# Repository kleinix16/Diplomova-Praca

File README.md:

# Diplomová práca - Komunikačný systém pre kameramanov

Autor: Bc. Tomáš Klein  
Vedúci práce:  prof. Ing. Juraj Miček, PhD.  
Registračné číslo:  28360820192562  
Rok vydania: Žilina, 2019 

Abstrakt: Diplomová práca sa zaoberá riešením problému komunikácie medzi režisérom a kameramanmi pri vytváraní kamerového záznamu pomocou zariadenia video-strižňa. Práca popisuje vytvorenie komunikačného systému, ktorý bude na kamery prenášať Tally svetelnú signalizáciu využitia kamier a krátke textové správy odosielané z Android zariadenia. V úvode práce je popísaná bezdrôtová komunikácia, so zameraním na bezlicenčné frekvenčné pásma. Ďalej práca obsahuje analýzu zadania, v ktorej je podrobnejšie rozobraný návrh celého systému. Táto časť obsahuje porovnanie a výber komponentov komunikačného systému. Implementačná časť práce sa venuje prepojeniu všetkých analyzovaných komponentov a obsahuje základné postupy a algoritmy, využívané pri riešení. 

Kľúčové slová:  ISM, Tally, Mikrokontrolér, Android, Bluetooth   

Súbory: dokumentácia, zdrojové kódy, android aplikácia, 3D model obalu, schémey, diagramy

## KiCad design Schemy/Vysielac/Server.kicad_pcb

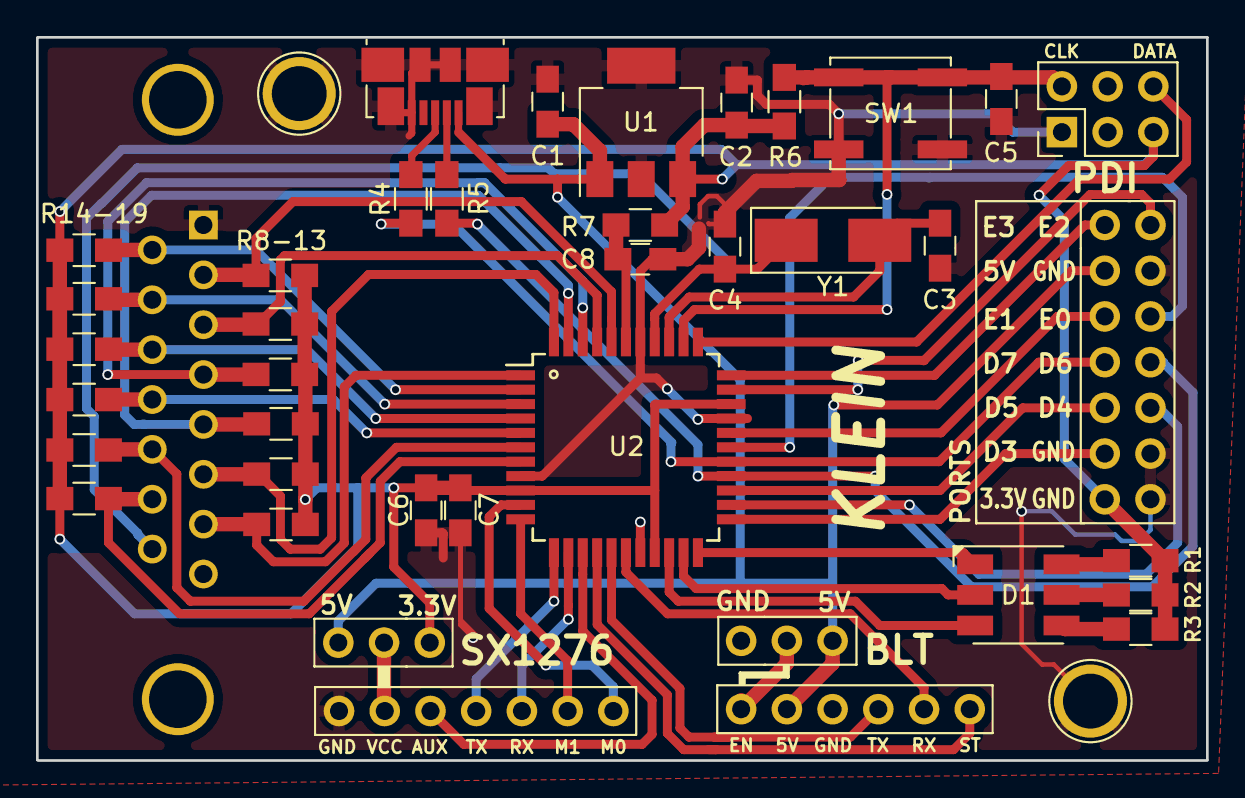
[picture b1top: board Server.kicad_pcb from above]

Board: 2 copper layers, 65.0 x 40.2 mm, 30 parts (0 on the bottom side), 37 nets.

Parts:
 : 1pin
 #2: USB_OTG; USB_Micro-B_Molex_47346-0001
 #3,  #4: Jumper; PIN_3_moj
 #5: PID; PIN_6_moj
 #6: Inter; PIN_12_moj
 #7: BLUETOOTH; PIN_6_moj
 #8: LoRa - SX1276; PIN_7_moj
C1, C5, C7, C8: M1; C_0805_HandSoldering
C2: 22M; C_0805_HandSoldering
C3, C4: C; C_0805_HandSoldering
C6: 2M2; C_0805_HandSoldering
D1: LED_RGB; LED_RGB_5050-6
R1, R2, R3, R4, R5, R14-19: R; R_0805_HandSoldering
R6: M1; R_0805_HandSoldering
R7: 100R; R_0805_HandSoldering
R8-13: 4k7; R_0805_HandSoldering
SW1: RESET; SW_SPST_EVQP0
U1: SOT 233; SOT-223-3_TabPin2
U2: ATXMEGA128A4-AU; CPU_moj
Y1: Crystal; Crystal_SMD_5032-2pin_5.0x3.2mm_HandSoldering

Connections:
+3V3: #3.1, #5.2, #6.13, C2.1, C6.1, C7.1, R1.2, R2.2, R3.2, R6.1, R7.2, R8-13.1, R14-19.1, U1.3, U2.9, U2.19, U2.31
+5V: #2.1, #3.3, #4.3, #6.3, #7.5, C1.1, U1.1
/L1: R14-19.2, U2.2
/R1: R8-13.2, U2.40
AUX_LORA: #8.5, U2.14
B_LED: D1.1, U2.22
GND: .1, #2.5, #2.6, #4.1, #5.6, #6.4, #6.12, #6.14, #7.4, #8.7, C1.2, C2.2, C3.1, C4.1, C5.1, C6.2, C7.2, C8.2, SW1.1, U1.2, U2.8, U2.18, U2.30, U2.38
G_LED: D1.2, U2.21
M0_LORA: #8.1, U2.10
M1_LORA: #8.2, U2.11
unnamed: C3.2, U2.36, Y1.2
unnamed: C4.2, U2.37, Y1.1
unnamed: C8.1, R7.1, U2.39
unnamed: D1.4, R3.1
unnamed: D1.5, R2.1
unnamed: D1.6, R1.1
unnamed: #2.2, R5.2
unnamed: #2.3, R4.2
unnamed: #4.2, #7.6
unnamed: #3.2, #8.6
PD3: #6.11, U2.23
PD4: #6.10, U2.24
PD5: #6.9, U2.25
PD6: #6.8, R5.1, U2.26
PD7: #6.7, R4.1, U2.27
PDI_CLK: #5.5, C5.2, R6.2, SW1.2, U2.35
PDI_DATA: #5.1, U2.34
PE0: #6.6, U2.28
PE1: #6.5, U2.29
PE2: #6.2, U2.32
PE3: #6.1, U2.33
RX_BLT: #7.2, U2.17
RX_LORA: #8.3, U2.13
R_LED: D1.3, U2.20
STATE_BLT: #7.1, U2.15
TX_BLT: #7.3, U2.16
TX_LORA: #8.4, U2.12

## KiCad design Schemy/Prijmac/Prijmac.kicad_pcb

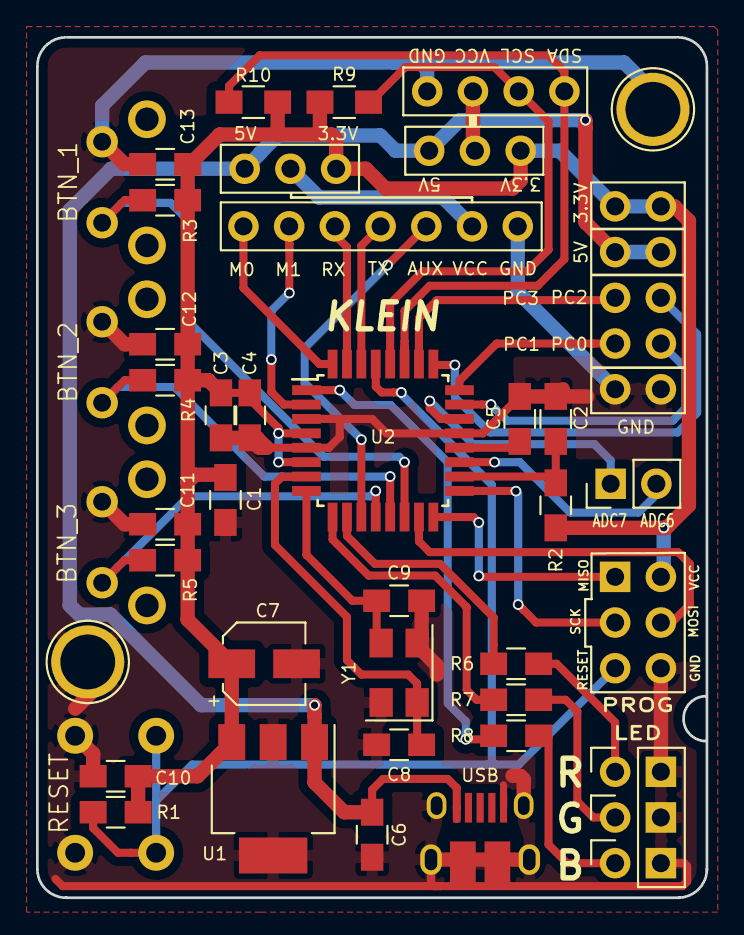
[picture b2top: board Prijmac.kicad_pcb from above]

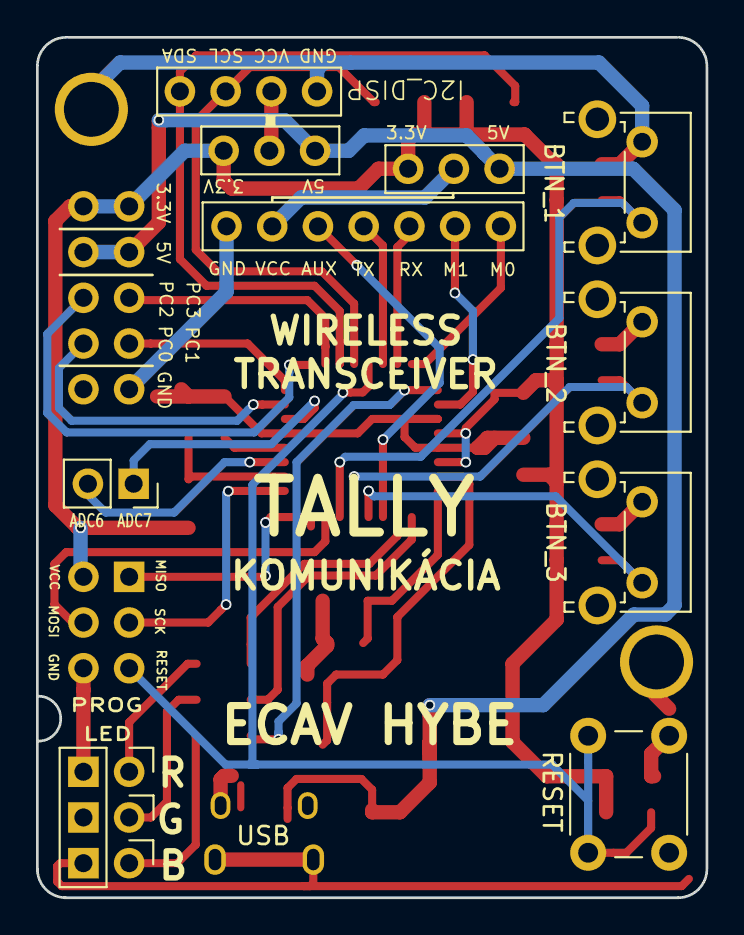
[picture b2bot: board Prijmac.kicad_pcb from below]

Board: 2 copper layers, 37.2 x 47.8 mm, 39 parts (5 on the bottom side), 35 nets.

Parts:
BTN_1, BTN_2, BTN_3: SW_Push; SW_Tactile_SPST_Angled_PTS645Vx83-2LFS
C1, C2, C4, C5, C6, C10, C11, C12, C13: M1; C_0805_HandSoldering
C3: 2M2; C_0805_HandSoldering
C7: 22M; CP_Elec_4x5.8
C8, C9: 18pF; C_0805_HandSoldering
J1: USB_OTG; USB_Micro-B_10103594-0001LF
J2: Analog_only; Pin_Header_Straight_1x02_Pitch2.54mm
J3: PROG; Pin_Header_Straight_2x03_Pitch2.54mm
J4: EXT; Pin_Header_Straight_2x05_Pitch2.54mm
J5: LEDS; Pin_Header_Straight_2x03_Pitch2.54mm
J6: LoRa - RFM; Pin_Header_Straight_1x07_Pitch2.54mm
J7: DISPLAY_I2C; Pin_Header_Straight_1x04_Pitch2.54mm
JP1, JP2: Jumper; Pin_Header_Straight_1x03_Pitch2.54mm
R1, R3, R4, R5, R6, R7, R8: R; C_0805_HandSoldering
R2: 100R; C_0805_HandSoldering
R9, R10: R; R_0805_HandSoldering
RESET: RESET; SW_PUSH_6mm
U1: SOT 233; SOT-223-3_TabPin2
U2: ATMEGA328P-AU; TQFP-32_7x7mm_Pitch0.8mm
Y1: Crystal_GND24; Crystal_SMD_5032-4pin_5.0x3.2mm

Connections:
+3V3: C1.1, C3.1, C4.1, C7.1, C10.1, C11.1, C12.1, C13.1, J3.2, J4.1, J4.2, JP1.1, JP2.1, R1.2, R2.2, R3.2, R4.2, R5.2, R9.1, R10.1, U1.3, U2.4, U2.6
+5V: C6.1, J1.1, J4.3, J4.4, JP1.3, JP2.3, U1.1
AUX_LORA: J6.5, U2.11
BTN_1: BTN_1.2, R3.1, U2.14
BTN_2: BTN_2.2, R4.1, U2.13
BTN_3: BTN_3.2, R5.1, U2.12
B_LED: R8.2, U2.1
GND: BTN_1.1, BTN_2.1, BTN_3.1, C1.2, C2.1, C3.2, C4.2, C5.1, C6.2, C7.2, C8.2, C9.2, C10.2, C11.2, C12.2, C13.2, J1.5, J1.6, J3.6, J4.9, J4.10, J5.2, J5.4, J5.6, J6.7, J7.4, RESET.1, U1.2, U2.3, U2.5, U2.21, Y1.2, Y1.4
G_LED: R7.2, U2.9
M0_LORA: J6.1, U2.32
M1_LORA: J6.2, U2.2
unnamed: C2.2, R2.1, U2.18
unnamed: C5.2, U2.20
unnamed: C8.1, U2.7, Y1.1
unnamed: C9.1, U2.8, Y1.3
unnamed: J2.1, U2.22
unnamed: J2.2, U2.19
unnamed: J3.1, U2.16
unnamed: J3.3, U2.17
unnamed: J3.4, U2.15
unnamed: J5.1, R6.1
unnamed: J5.3, R7.1
unnamed: J5.5, R8.1
unnamed: J6.6, JP1.2
unnamed: J7.3, JP2.2
PC0: J4.8, U2.23
PC1: J4.7, U2.24
PC2: J4.6, U2.25
PC3: J4.5, U2.26
RESET: J3.5, R1.1, RESET.2, U2.29
RX_LORA: J6.3, U2.31
R_LED: R6.2, U2.10
SCL: J7.2, R9.2, U2.28
SDA: J7.1, R10.2, U2.27
TX_LORA: J6.4, U2.30

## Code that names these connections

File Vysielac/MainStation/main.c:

/*
 * MainStation.c
 *
 * Created: 12/22/2018 10:14:10 AM
 * Author : klein
 */

#include "avr_compiler.h"
#include "board.h"
#include "usart_driver.h"
#include "port_driver.h"
#include "TC_driver.h"

#include <util/delay.h>
#include <stdio.h>
#include <string.h>
#include <avr/io.h>

//USART riesim za pomoci dodavanych zdrojakov -projekt AVR1522 - 2 task

//RFM
//USART_RFM Defines
#define USART_RFM USARTC0
#define USART_PORT_RFM PORTC

/* USART data struct used in task */
USART_data_t USART_data_RFM;

//PC
//USART_PC Defines
#define USART_PC USARTE0
#define USART_PORT_PC PORTE

/* USART data struct used in task */
USART_data_t USART_data_PC;
/*
volatile	uint8_t port_A;   //Ulozena posledna hodnota na porte A
volatile	uint8_t port_B;	  //Ulozena posledna hodnota na porte B*/

volatile uint8_t STATE = 0x00;     // Bajt hovoriaci o dovode, preco sa sprava odoslala
volatile uint8_t CAM_READY = 0x00; // Cislo kamery v pripravnom rezime
volatile uint8_t CAM_LIVE = 0x00;  // Cislo kamery v ostrom vyslieani

volatile uint8_t port_A;
volatile uint8_t port_B;

void setTally_CONN()
{
    PORTA.PIN1CTRL = PORT_OPC_PULLUP_gc;
    PORTA.PIN2CTRL = PORT_OPC_PULLUP_gc;
    PORTA.PIN3CTRL = PORT_OPC_PULLUP_gc;
    PORTA.PIN4CTRL = PORT_OPC_PULLUP_gc;
    PORTA.PIN5CTRL = PORT_OPC_PULLUP_gc;
    PORTA.PIN6CTRL = PORT_OPC_PULLUP_gc;
    PORTA.PIN7CTRL = PORT_OPC_PULLUP_gc;
    PORTA.PIN0CTRL = PORT_OPC_PULLUP_gc;
    PORTB.PIN0CTRL = PORT_OPC_PULLUP_gc;
    PORTB.PIN1CTRL = PORT_OPC_PULLUP_gc;
    PORTB.PIN2CTRL = PORT_OPC_PULLUP_gc;
    PORTB.PIN3CTRL = PORT_OPC_PULLUP_gc;

    PORT_SetPinsAsInput(&PORTA, 0xFF);
    PORT_SetPinsAsInput(&PORTB, 0x0F);
}

void setUp_RFM_USART()
{
    /*
	 *    USART configuration:
	 *      - 8 bit character size
	 *      - No parity
	 *      - 1 stop bit
	 *      - 9600 Baud
	 */

    /* PC3 (TXD0) as output. */
    USART_PORT_RFM.DIRSET = PIN3_bm;

    /* PC2 (RXD0) as input. */
    USART_PORT_RFM.DIRCLR = PIN2_bm;

    /* M0 - nastavenie na nulu */
    USART_PORT_RFM.DIRSET = PIN0_bm;
    USART_PORT_RFM.OUTCLR = PIN0_bm;

    /* M1 - nastavenie na nulu */
    USART_PORT_RFM.DIRSET = PIN1_bm;
    USART_PORT_RFM.OUTCLR = PIN1_bm;

    /* Use USARTx0 and initialize buffers */
    USART_InterruptDriver_Initialize(&USART_data_RFM, &USART_RFM, USART_DREINTLVL_LO_gc);

    /* USART, 8 Data bits, No Parity, 1 Stop bit. */
    USART_Format_Set(&USART_RFM, USART_CHSIZE_8BIT_gc, USART_PMODE_DISABLED_gc, false);

    /* Enable RXC interrupt */
    //USART_RxdInterruptLevel_Set(USART_data_RFM.usart, USART_RXCINTLVL_LO_gc);
    USART_RxdInterruptLevel_Set(&USART_RFM, USART_RXCINTLVL_LO_gc);

    /* Set Baudrate to 9600 bps:
	 * Use the default I/O clock fequency that is 2 MHz.
	 * Do not use the baudrate scale factor
	 *
	 * Baudrate select = (1/(16*(((I/O clock frequency)/Baudrate)-1)
	 *                 = 12
	 */
    USART_Baudrate_Set(&USART_RFM, 12, 0);

    /* Enable both RX and TX. */
    USART_Rx_Enable(&USART_RFM);
    USART_Tx_Enable(&USART_RFM);
}

void setUp_PC_USART()
{
    /*
	 *    USART configuration:
	 *      - 8 bit character size
	 *      - No parity
	 *      - 1 stop bit
	 *      - 9600 Baud
	 */

    /* PE3 (TXD0) as output. */
    USART_PORT_PC.DIRSET = PIN3_bm;

    /* PE2 (RXD0) as input. */
    USART_PORT_PC.DIRCLR = PIN2_bm;

    /* Use USARTx0 and initialize buffers */
    USART_InterruptDriver_Initialize(&USART_data_PC, &USART_PC, USART_DREINTLVL_LO_gc);

    /* USART, 8 Data bits, No Parity, 1 Stop bit. */
    USART_Format_Set(&USART_PC, USART_CHSIZE_8BIT_gc, USART_PMODE_DISABLED_gc, false);

    /* Enable RXC interrupt */
    //USART_RxdInterruptLevel_Set(USART_data_RFM.usart, USART_RXCINTLVL_LO_gc);
    USART_RxdInterruptLevel_Set(&USART_PC, USART_RXCINTLVL_LO_gc);

    /* Set Baudrate to 9600 bps:
	 * Use the default I/O clock fequency that is 2 MHz.
	 * Do not use the baudrate scale factor
	 *
	 * Baudrate select = (1/(16*(((I/O clock frequency)/Baudrate)-1)
	 *                 = 12
	 */
    USART_Baudrate_Set(&USART_PC, 12, 0);

    /* Enable both RX and TX. */
    USART_Rx_Enable(&USART_PC);
    USART_Tx_Enable(&USART_PC);
}

void setTimer_Beacon()
{
    /* Set the TC period. */  
    TC_SetPeriod(&TCC0, 0x2710); //5000ms

    /* Enable overflow interrupt at low level */
    TC0_SetOverflowIntLevel(&TCC0, TC_OVFINTLVL_LO_gc);

    /* Start Timer/Counter. */
    TC0_ConfigClockSource(&TCC0, TC_CLKSEL_DIV1024_gc);
}


void setTimer_Tally()
{
    /* Set the TC period. */
    TC_SetPeriod(&TCC1, 0x0190);  //200ms

    /* Enable overflow interrupt at low level */
    TC1_SetOverflowIntLevel(&TCC1, TC_OVFINTLVL_LO_gc);

    /* Start Timer/Counter. */
    TC1_ConfigClockSource(&TCC1, TC_CLKSEL_DIV1024_gc);
	
}

void sendStatus_RFM()
{

    while (!(USARTC0_STATUS & USART_DREIF_bm))
        ; //Wait until DATA buffer is empty

    USARTC0_DATA = STATE;

    while (!(USARTC0_STATUS & USART_DREIF_bm))
        ; //Wait until DATA buffer is empty

    USARTC0_DATA = CAM_LIVE;

    while (!(USARTC0_STATUS & USART_DREIF_bm))
        ; //Wait until DATA buffer is empty

    USARTC0_DATA = CAM_READY;
	
	while (!(USARTC0_STATUS & USART_DREIF_bm))
	; //Wait until DATA buffer is empty

	USARTC0_DATA = 'a';

/*
    while (!(USARTC0_STATUS & USART_DREIF_bm))
        ; //Wait until DATA buffer is empty

    USARTC0_DATA = '\n';

    while (!(USARTC0_STATUS & USART_DREIF_bm))
        ; //Wait until DATA buffer is empty

    USARTC0_DATA = '\r';
	*/

    STATE = 0;
}

void sendChar(char c)
{

    while (!(USARTC0_STATUS & USART_DREIF_bm))
        ; //Wait until DATA buffer is empty

    USARTC0_DATA = c;
}

void sendString(char *text)
{
    while (*text)
    {
        sendChar(*text++);
    }
}

int main(void)
{
    setUp_RFM_USART();

    setUp_PC_USART();

    setTimer_Beacon();
	
	setTimer_Tally();



    // Enable all interrupt levels in PMIC and enable global interrupts.
    PMIC.CTRL |= PMIC_LOLVLEN_bm | PMIC_MEDLVLEN_bm | PMIC_HILVLEN_bm;
    sei();

    while (1)
    {
        if (STATE == 1 || STATE == 2)
        {
            sendStatus_RFM();
        }
        _delay_ms(20);

        /*
	   	  if (USART_RXBufferData_Available(&USART_data_PC))
	   	  {
		   	  sendChar(USART_RXBuffer_GetByte(&USART_data_PC));	  
	   	  }*/
    }
}

/*! \brief Receive complete interrupt service routine.
 *
 *  Receive complete interrupt service routine.
 *  Calls the common receive complete handler with pointer to the correct USART
 *  as argument.
 */
ISR(USARTC0_RXC_vect)
{
    USART_RXComplete(&USART_data_RFM);
}

ISR(USARTE0_RXC_vect)
{
    USART_RXComplete(&USART_data_PC);
}

ISR(USARTC0_DRE_vect)
{
    USART_DataRegEmpty(&USART_data_RFM);
}

ISR(USARTE0_DRE_vect)
{
    USART_DataRegEmpty(&USART_data_PC);
}

// Tell compiler to associate this interrupt handler with the TCC0_OVF_vect vector.
ISR(TCC1_OVF_vect) // TALLY
{
    uint8_t port_A_temp = PORT_GetPortValue(&PORTA);
    uint8_t port_B_temp = PORT_GetPortValue(&PORTB);

    if (port_A_temp != port_A || port_B_temp != port_B)
    {
        port_A = port_A_temp;
        port_B = port_B_temp;

        CAM_LIVE = ((port_A & 0xC0) >> 2) + port_B;
        CAM_READY = port_A >> 2;

        STATE = 2; //Odoslanie dat pri zmene na portoch
		TC_Restart( &TCC0 );
    }
}

ISR(TCC0_OVF_vect) // BEACON 
{
    STATE = 1; //Pravidelne zasielanie dat
}

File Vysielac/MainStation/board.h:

/*
 * board.h
 *
 * Created: 6/3/2018 1:47:07 PM
 *  Author: klein
 */ 


#ifndef BOARD_H_
#define BOARD_H_



#include <avr/io.h>

#define sbi(x,y) x |= _BV(y)	 //set bit     (1<<y)
#define cbi(x,y) x &= ~(_BV(y)) //clear bit - using bitwise AND operator
#define tbi(x,y) x ^= _BV(y)    //change bit - using bitwise XOR operator

#define R_LED  PORTD0
#define B_LED  PORTD1
#define G_LED  PORTD2

#define BLT_RX  PORTC7
#define BLT_TX  PORTC6
#define BLT_STATE  PORTC5

#define USB_DP  PORTD7
#define USB_DM  PORTD6

#define LORA_RX  PORTC3
#define LORA_TX  PORTC2
#define LORA_M0  PORTC0
#define LORA_M1  PORTC1
#define LORA_AUX  PORTC4

#define TALLY_R1  PORTA0
#define TALLY_R2  PORTA1
#define TALLY_R3  PORTA2
#define TALLY_R4  PORTA3
#define TALLY_R5  PORTA4
#define TALLY_R6  PORTA5

#define TALLY_L1  PORTA6
#define TALLY_L2  PORTA7
#define TALLY_L3  PORTB0
#define TALLY_L4  PORTB1
#define TALLY_L5  PORTB2
#define TALLY_L6  PORTB3

#endif /* BOARD_H_ */

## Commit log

2019-01-24 Add files via upload
    Pre nahranie suborov, sparovanie dosiek, nutnost reviyei kodu
2019-01-24 Skuska commitu z PC
2019-01-24 Uprava nazvu priecinkov
2019-01-24 Revizia kodu prijmaca - formalne stranky
2019-01-24 Revizia kodu vysielaca - formalne stranky, bude treba ale viac okomentovat kod
2019-01-26 Pridanie funkcnej casti kodu na ovladanie I2C displeja, nutnost integracie a revizie kodu
2019-01-26 Pridanie schem do GIT priecinku
2019-01-26 synchronyzovanie zobrazovania aktualnej kamery na displej
2019-01-27 Dokoncenie aktual prace na doskach prechod na posielanie sprav cez bluetooth
2019-01-30 Pirdanie Android aplikacie vztvorenej cez MIT inventor a dorobenie BLT - RFM brany na vysielaci
2019-01-31 Pridanie dokumentácie na Projektovú výučbu
2019-02-02 Zaloha pred zavaynovu upravou Riadiacej jednotky - synchronizacia
2019-02-02 Riadiaca jednotka upravena - vyzera ze synchronizacia odosielania dat funguje - presobeny cely system
2019-02-03 Dost nefunkca uprava krhoveho buffera
2019-02-03 Vyzera ze funkcny buffer aj pre spravy
2019-02-03 Pridanie zobrazovnia sprav podla indexu, zobrazenie na displeji s casovacom - 10 sekund
2019-02-16 Prijmac - implementacia tlacidiel a to vsetko uz na novej soske
2019-03-02 pridanie textov do wordu
2019-03-19 pokrok v texte
2019-03-23 Upravene schemy
2019-03-29 uprava zloziek a kodu signalizacnej jednotky
2019-03-30 Hruba editacia textu ukoncena
2019-03-30 Pridanie abstraktu a uprava referencii
2019-03-31 Kod v1.0
2019-03-31 Doc bez finalnych obrazkov
2019-03-31 Update README.md
    Add README
2019-03-31 Pridanie testovacich obrazkov - poslane na kontrolu chyb
2019-04-09 Odovzdanie prace
2019-04-09 Uprava priecinkov a odstranenie chyby SJ s Live signalizaciou
2019-04-09 Odovdanie veducemu prace - pripojene multimedia
2019-07-13 ing - hotovo
